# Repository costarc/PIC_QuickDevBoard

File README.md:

# PIC_QuickDevBoard
Small and simple PIC16F &amp; PIC24F Development Board with Programming Support for PICKit

Rev 2.3
- Added demo project for all three suported PIC models
- Changed LED to PORT RB4 to be compatible with the 3 PICs supported by the board
- Added missing terminals in the mini-usb custom footprint
- Changed LED resistor from 270R to 470R to avoid led light too bright
- Changed PIC16F84 /MCLR pull-up resistor from 270R to 10K

Rev 2.2
- Adjustments to mini-usb footprint
- Fixed power rails to PC16F145X that was not allowing programming the microcontroller

Rev 2.1
- Updated footprint for USB-Micro to move it to the comopnent side (vcc - gnd was inverted)
- Fix for 5V PICs (16F) with addtion o extra jumpers
- Inverted PICKIT pin header for better alignment (cosmetic change)

Rev 2.0
- Initial production version

Fabrication
-----------
Measures: 70.90 x 81.30

Usage
-----

Power Requirements - PIC16
--------------------------

For correct programing, erasing and verifying the PIC, the external porwer must be provided via the USB connector or the PIN Header.

PIC16 requires 5V - if the PIN Header is used for power, 5V should be provided in this connector.
USB connector will provide the correct 5V for the PIC16.

Power Requirements - PIC24
--------------------------

For correct programing, erasing and verifying the PIC, the external porwer must be provided via the USB connector or the PIN Header.

PIC24 requires 3.3V - if the PIN Header is used for power, 3.3V must be provided in this connector - no conversion is done for voltages provided via this connector.
USB connector will provide the correct 3.3V for the PIC24 via coversion using the LD1117 converter in the board.

Operation * Programming
-----------------------

To develop & program A PIC device, set the three jumpers in position PIC24F, PIC16F14 OR PIC16F84 depending on which device you are being used.

To program the PIC24, remove jumper "Program". Re-insert after programming.

Development Resources
---------------------
All  I/O pins are exposed thorugh the Pin Headers in the board.
Additionaly, a Pushb Button and a LED are available for quick tests and experiments.
Push Button is connected to RA0
LED is connected to RB4

These components can be removed from the board if they are not needed or if they interfere with normal operation of these signals in the Pin Headers.

Default Demonstration Firmware
------------------------------
The demonstration firmware works the same for all models - the LED on RB4 will blink slowly, but if the push button is pressed it will blink faster.

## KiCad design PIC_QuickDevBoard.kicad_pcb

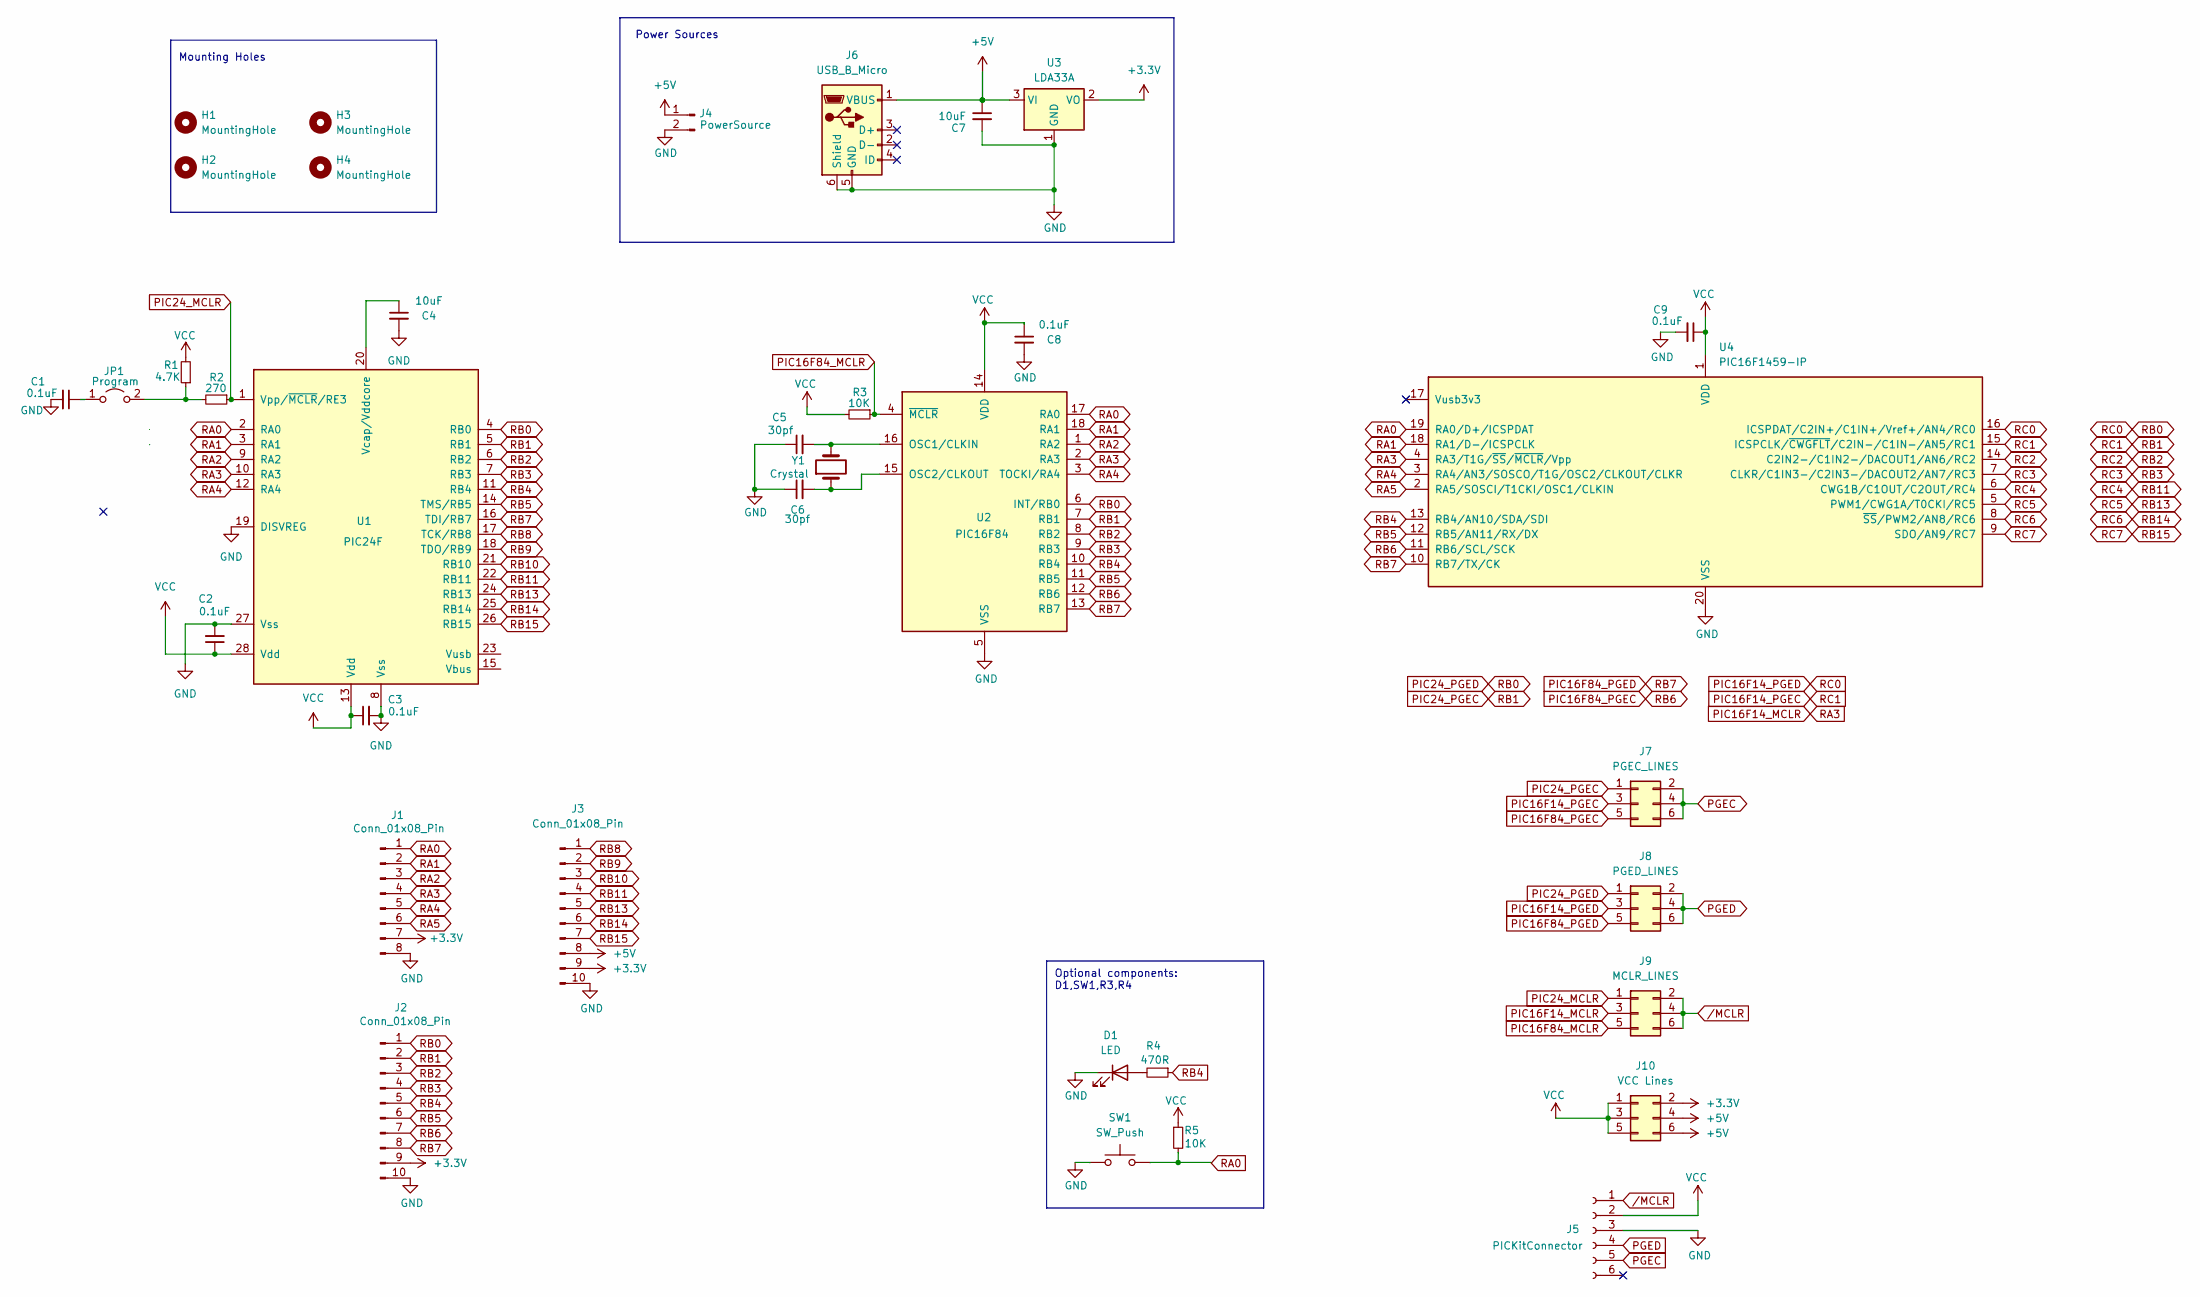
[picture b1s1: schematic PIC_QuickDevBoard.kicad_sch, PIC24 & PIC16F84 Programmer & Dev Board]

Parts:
C1, C2, C3, C8, C9: 0.1uF; C_Disc_D3.4mm_W2.1mm_P2.50mm
C4: 10uF; CP_Radial_Tantal_D4.5mm_P2.50mm
C5, C6: 30pf; C_Disc_D3.4mm_W2.1mm_P2.50mm
C7: 10uF; CP_Radial_D6.3mm_P2.50mm
D1: LED; LED_D3.0mm
H1, H2, H3, H4: MountingHole; MountingHole_2.5mm_Pad
J1: Conn_01x08_Pin; PinHeader_1x08_P2.54mm_Vertical
J2, J3: Conn_01x08_Pin; PinHeader_1x10_P2.54mm_Vertical
J4: PowerSource; PinHeader_1x02_P2.54mm_Vertical
J5: PICKitConnector; PinHeader_1x06_P2.54mm_Vertical
J6: USB_B_Micro; USB_Mini-B_Tensility_4Holes
J7: PGEC_LINES; PinHeader_2x03_P2.00mm_Vertical
J8: PGED_LINES; PinHeader_2x03_P2.00mm_Vertical
J9: MCLR_LINES; PinHeader_2x03_P2.00mm_Vertical
J10: VCC Lines; PinHeader_2x03_P2.00mm_Vertical
JP1: Program; PinHeader_1x02_P2.54mm_Vertical
R1: 4.7K; R_Axial_DIN0207_L6.3mm_D2.5mm_P7.62mm_Horizontal
R2: 270; R_Axial_DIN0207_L6.3mm_D2.5mm_P7.62mm_Horizontal
R3, R5: 10K; R_Axial_DIN0207_L6.3mm_D2.5mm_P7.62mm_Horizontal
R4: 470R; R_Axial_DIN0207_L6.3mm_D2.5mm_P7.62mm_Horizontal
SW1: SW_Push; SW_PUSH_6mm_2Holes
U1: PIC24F; DIP-28_W7.62mm
U2: PIC16F84; DIP-18_W7.62mm
U3: LDA33A; SOT-223-3_TabPin2
U4: PIC16F1459-IP; DIP-20_W7.62mm
Y1: Crystal; Crystal_HC49-U_Vertical

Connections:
+3.3V: J1.7, J2.9, J3.9, J10.2, U3.2 (VO)
+5V: C7.1, J3.8, J4.1, J6.1 (VBUS), J10.4, J10.6, U3.3 (VI)
GND: C1.2, C2.2, C3.2, C4.2, C5.1, C6.1, C7.2, C8.2, C9.2, D1.1 (K), J1.8, J2.10, J3.10, J4.2, J5.3, J6.5 (GND), J6.6 (Shield), SW1.1, U1.8 (Vss), U1.19 (DISVREG), U1.27 (Vss), U2.5 (VSS), U3.1 (GND), U4.20 (VSS)
unnamed: D1.2 (A), R4.2
unnamed: C1.1, JP1.1 (A)
unnamed: JP1.2 (B), R1.1, R2.2
unnamed: C4.1, U1.20 (Vcap/Vddcore)
unnamed: C5.2, U2.16 (OSC1/CLKIN), Y1.2
unnamed: C6.2, U2.15 (OSC2/CLKOUT), Y1.1
PGEC: J5.5, J7.2, J7.4, J7.6
PGED: J5.4, J8.2, J8.4, J8.6
PIC16F14_MCLR: J1.4, J9.3, U1.10 (RA3), U2.2 (RA3), U4.4 (RA3/T1G/~SS/~MCLR/Vpp)
PIC16F14_PGEC: J2.2, J7.1, J7.3, U1.5 (RB1), U2.7 (RB1), U4.15 (ICSPCLK/~CWGFLT/C2IN-/C1IN-/AN5/RC1)
PIC16F14_PGED: J2.1, J8.1, J8.3, U1.4 (RB0), U2.6 (INT/RB0), U4.16 (ICSPDAT/C2IN+/C1IN+/Vref+/AN4/RC0)
PIC16F84_MCLR: J9.5, R3.1, U2.4 (~MCLR)
PIC16F84_PGEC: J2.7, J7.5, U2.12 (RB6), U4.11 (RB6/SCL/SCK)
PIC16F84_PGED: J2.8, J8.5, U1.16 (TDI/RB7), U2.13 (RB7), U4.10 (RB7/TX/CK)
PIC24_MCLR: J9.1, R2.1, U1.1 (Vpp/~MCLR/RE3)
RA0: J1.1, R5.2, SW1.2, U1.2 (RA0), U2.17 (RA0), U4.19 (RA0/D+/ICSPDAT)
RA1: J1.2, U1.3 (RA1), U2.18 (RA1), U4.18 (RA1/D-/ICSPCLK)
RA2: J1.3, U1.9 (RA2), U2.1 (RA2)
RA4: J1.5, U1.12 (RA4), U2.3 (TOCKI/RA4), U4.3 (RA4/AN3/SOSCO/T1G/OSC2/CLKOUT/CLKR)
RA5: J1.6, U4.2 (RA5/SOSCI/T1CKI/OSC1/CLKIN)
RB2: J2.3, U1.6 (RB2), U2.8 (RB2), U4.14 (C2IN2-/C1IN2-/DACOUT1/AN6/RC2)
RB3: J2.4, U1.7 (RB3), U2.9 (RB3), U4.7 (CLKR/C1IN3-/C2IN3-/DACOUT2/AN7/RC3)
RB4: J2.5, R4.1, U1.11 (RB4), U2.10 (RB4), U4.13 (RB4/AN10/SDA/SDI)
RB5: J2.6, U1.14 (TMS/RB5), U2.11 (RB5), U4.12 (RB5/AN11/RX/DX)
RB8: J3.1, U1.17 (TCK/RB8)
RB9: J3.2, U1.18 (TDO/RB9)
RB10: J3.3, U1.21 (RB10)
RB11: J3.4, U1.22 (RB11), U4.6 (CWG1B/C1OUT/C2OUT/RC4)
RB13: J3.5, U1.24 (RB13), U4.5 (PWM1/CWG1A/T0CKI/RC5)
RB14: J3.6, U1.25 (RB14), U4.8 (~SS/PWM2/AN8/RC6)
RB15: J3.7, U1.26 (RB15), U4.9 (SDO/AN9/RC7)
VCC: C2.1, C3.1, C8.1, C9.1, J5.2, J10.1, J10.3, J10.5, R1.2, R3.2, R5.1, U1.13 (Vdd), U1.28 (Vdd), U2.14 (VDD), U4.1 (VDD)
/MCLR: J5.1, J9.2, J9.4, J9.6

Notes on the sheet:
Optional components: D1,SW1,R3,R4
Mounting Holes
Power Sources

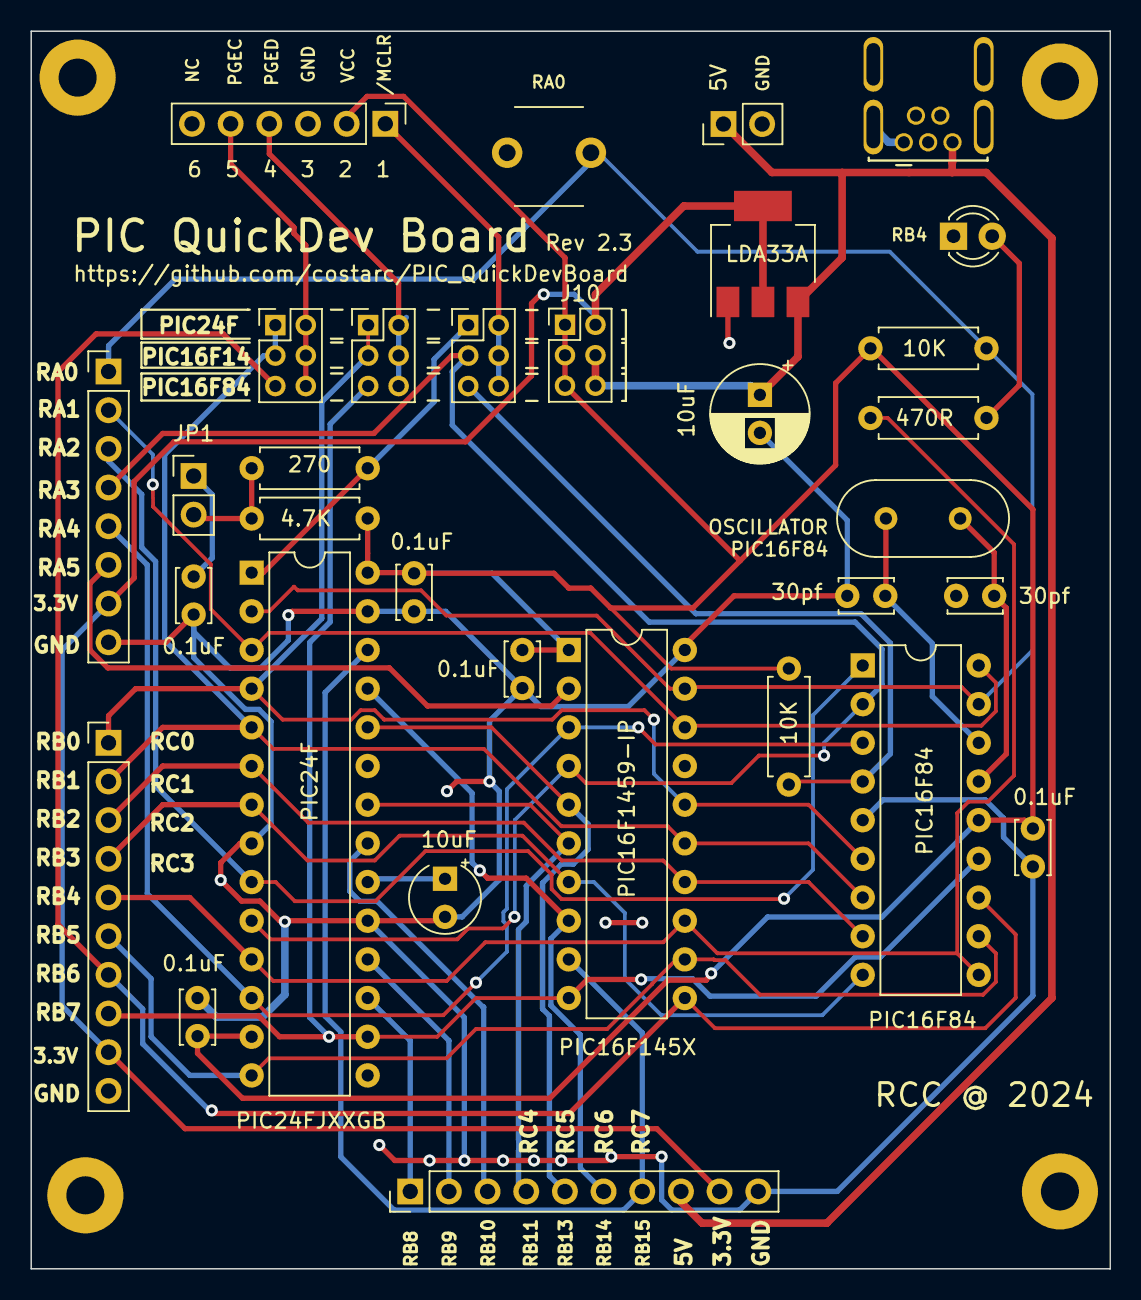
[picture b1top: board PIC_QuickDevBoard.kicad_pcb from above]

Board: 2 copper layers, 70.9 x 81.3 mm, 36 parts (0 on the bottom side), 36 nets.

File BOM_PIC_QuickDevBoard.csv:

"Reference","Value","Datasheet","Footprint","Qty","DNP"
"C1,C2,C3,C8,C9","0.1uF","~","Capacitor_THT:C_Disc_D3.4mm_W2.1mm_P2.50mm","5",""
"C4,C7","10uF","~","-- mixed values --","2",""
"C5,C6","30pf","~","Capacitor_THT:C_Disc_D3.4mm_W2.1mm_P2.50mm","2",""
"D1","LED","~","LED_THT:LED_D3.0mm","1",""
"H1,H2,H3,H4","MountingHole","~","MountingHole:MountingHole_2.5mm_Pad","4",""
"J1,J2,J3","Conn_01x08_Pin","~","-- mixed values --","3",""
"J4","PowerSource","~","Connector_PinHeader_2.54mm:PinHeader_1x02_P2.54mm_Vertical","1",""
"J5","PICKitConnector","~","Connector_PinHeader_2.54mm:PinHeader_1x06_P2.54mm_Vertical","1",""
"J6","USB_B_Micro","~","Roni_Footprints:USB_Mini-B_Tensility_4Holes","1",""
"J7","PGEC_LINES","~","Connector_PinHeader_2.00mm:PinHeader_2x03_P2.00mm_Vertical","1",""
"J8","PGED_LINES","~","Connector_PinHeader_2.00mm:PinHeader_2x03_P2.00mm_Vertical","1",""
"J9","MCLR_LINES","~","Connector_PinHeader_2.00mm:PinHeader_2x03_P2.00mm_Vertical","1",""
"J10","VCC Lines","~","Connector_PinHeader_2.00mm:PinHeader_2x03_P2.00mm_Vertical","1",""
"JP1","Program","~","Connector_PinHeader_2.54mm:PinHeader_1x02_P2.54mm_Vertical","1",""
"R1","4.7K","~","Resistor_THT:R_Axial_DIN0207_L6.3mm_D2.5mm_P7.62mm_Horizontal","1",""
"R2","270","~","Resistor_THT:R_Axial_DIN0207_L6.3mm_D2.5mm_P7.62mm_Horizontal","1",""
"R3,R5","10K","~","Resistor_THT:R_Axial_DIN0207_L6.3mm_D2.5mm_P7.62mm_Horizontal","2",""
"R4","470R","~","Resistor_THT:R_Axial_DIN0207_L6.3mm_D2.5mm_P7.62mm_Horizontal","1",""
"SW1","SW_Push","~","Roni_Footprints:SW_PUSH_6mm_2Holes","1",""
"U1","PIC24F","http://ww1.microchip.com/downloads/en/DeviceDoc/41452B.pdf","Package_DIP:DIP-28_W7.62mm","1",""
"U2","PIC16F84","http://ww1.microchip.com/downloads/en/DeviceDoc/30430c.pdf","Package_DIP:DIP-18_W7.62mm","1",""
"U3","LDA33A","http://www.st.com/st-web-ui/static/active/en/resource/techni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","Package_TO_SOT_SMD:SOT-223-3_TabPin2","1",""
"U4","PIC16F1459-IP","http://ww1.microchip.com/downloads/en/DeviceDoc/41639A.pdf","Package_DIP:DIP-20_W7.62mm","1",""
"Y1","Crystal","~","Crystal:Crystal_HC49-U_Vertical","1",""

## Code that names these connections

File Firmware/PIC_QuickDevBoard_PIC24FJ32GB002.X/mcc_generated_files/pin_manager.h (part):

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*/
/**
  @Summary
    Sets the GPIO pin, RA0, high using LATA0.

  @Description
    Sets the GPIO pin, RA0, high using LATA0.

  @Preconditions
    The RA0 must be set to an output.
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#define BUTTON_SetHigh()          (_LATA0 = 1)
/**
  @Summary
    Sets the GPIO pin, RA0, low using LATA0.

  @Description
    Sets the GPIO pin, RA0, low using LATA0.

  @Preconditions
    The RA0 must be set to an output.
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#define BUTTON_SetLow()           (_LATA0 = 0)
/**
  @Summary
    Toggles the GPIO pin, RA0, using LATA0.

  @Description
    Toggles the GPIO pin, RA0, using LATA0.

  @Preconditions
    The RA0 must be set to an output.
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#define BUTTON_Toggle()           (_LATA0 ^= 1)
/**
  @Summary
    Reads the value of the GPIO pin, RA0.

  @Description
    Reads the value of the GPIO pin, RA0.

  @Preconditions
    None.
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    </code>

*/
#define BUTTON_GetValue()         _RA0
/**
  @Summary
    Configures the GPIO pin, RA0, as an input.

  @Description
    Configures the GPIO pin, RA0, as an input.

  @Preconditions
    None.
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#define BUTTON_SetDigitalInput()  (_TRISA0 = 1)
/**
  @Summary
    Configures the GPIO pin, RA0, as an output.

  @Description
    Configures the GPIO pin, RA0, as an output.

  @Preconditions
    None.
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#define BUTTON_SetDigitalOutput() (_TRISA0 = 0)
/**
  @Summary
    Sets the GPIO pin, RA1, high using LATA1.

  @Description
    Sets the GPIO pin, RA1, high using LATA1.

  @Preconditions
    The RA1 must be set to an output.
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#define IO_RA1_SetHigh()          (_LATA1 = 1)
/**
  @Summary
    Sets the GPIO pin, RA1, low using LATA1.

  @Description
    Sets the GPIO pin, RA1, low using LATA1.

  @Preconditions
    The RA1 must be set to an output.
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#define IO_RA1_SetLow()           (_LATA1 = 0)
/**
  @Summary
    Toggles the GPIO pin, RA1, using LATA1.

  @Description
    Toggles the GPIO pin, RA1, using LATA1.

  @Preconditions
    The RA1 must be set to an output.
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#define IO_RA1_Toggle()           (_LATA1 ^= 1)
/**
  @Summary
    Reads the value of the GPIO pin, RA1.

  @Description
    Reads the value of the GPIO pin, RA1.

  @Preconditions
    None.
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    </code>

*/
#define IO_RA1_GetValue()         _RA1
/**
  @Summary
    Configures the GPIO pin, RA1, as an input.

  @Description
    Configures the GPIO pin, RA1, as an input.

  @Preconditions
    None.
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#define IO_RA1_SetDigitalInput()  (_TRISA1 = 1)
/**
  @Summary
    Configures the GPIO pin, RA1, as an output.

  @Description
    Configures the GPIO pin, RA1, as an output.

  @Preconditions
    None.
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#define IO_RA1_SetDigitalOutput() (_TRISA1 = 0)
/**
  @Summary
    Sets the GPIO pin, RA2, high using LATA2.

  @Description
    Sets the GPIO pin, RA2, high using LATA2.

  @Preconditions
    The RA2 must be set to an output.
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#define IO_RA2_SetHigh()          (_LATA2 = 1)
/**
  @Summary
    Sets the GPIO pin, RA2, low using LATA2.

  @Description
    Sets the GPIO pin, RA2, low using LATA2.

  @Preconditions
    The RA2 must be set to an output.
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#define IO_RA2_SetLow()           (_LATA2 = 0)
/**
  @Summary
    Toggles the GPIO pin, RA2, using LATA2.

  @Description
    Toggles the GPIO pin, RA2, using LATA2.

  @Preconditions
    The RA2 must be set to an output.
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#define IO_RA2_Toggle()           (_LATA2 ^= 1)
/**
  @Summary
    Reads the value of the GPIO pin, RA2.

  @Description
    Reads the value of the GPIO pin, RA2.

  @Preconditions
    None.
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    </code>

*/
#define IO_RA2_GetValue()         _RA2
/**
  @Summary
    Configures the GPIO pin, RA2, as an input.

  @Description
    Configures the GPIO pin, RA2, as an input.

  @Preconditions
    None.
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#define IO_RA2_SetDigitalInput()  (_TRISA2 = 1)
/**
  @Summary
    Configures the GPIO pin, RA2, as an output.

  @Description
    Configures the GPIO pin, RA2, as an output.

  @Preconditions
    None.
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#define IO_RA2_SetDigitalOutput() (_TRISA2 = 0)
/**
  @Summary
    Sets the GPIO pin, RA3, high using LATA3.

  @Description
    Sets the GPIO pin, RA3, high using LATA3.

  @Preconditions
    The RA3 must be set to an output.
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#define IO_RA3_SetHigh()          (_LATA3 = 1)
/**
  @Summary
    Sets the GPIO pin, RA3, low using LATA3.

  @Description
    Sets the GPIO pin, RA3, low using LATA3.

  @Preconditions
    The RA3 must be set to an output.
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#define IO_RA3_SetLow()           (_LATA3 = 0)
/**
  @Summary
    Toggles the GPIO pin, RA3, using LATA3.

  @Description
    Toggles the GPIO pin, RA3, using LATA3.

  @Preconditions
    The RA3 must be set to an output.
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#define IO_RA3_Toggle()           (_LATA3 ^= 1)
/**
  @Summary
    Reads the value of the GPIO pin, RA3.

  @Description
    Reads the value of the GPIO pin, RA3.

  @Preconditions
    None.
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    </code>

*/
#define IO_RA3_GetValue()         _RA3
/**
  @Summary
    Configures the GPIO pin, RA3, as an input.

  @Description
    Configures the GPIO pin, RA3, as an input.

  @Preconditions
    None.
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#define IO_RA3_SetDigitalInput()  (_TRISA3 = 1)
/**
  @Summary
    Configures the GPIO pin, RA3, as an output.

  @Description
    Configures the GPIO pin, RA3, as an output.

  @Preconditions
    None.
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#define IO_RA3_SetDigitalOutput() (_TRISA3 = 0)
/**
  @Summary
    Sets the GPIO pin, RA4, high using LATA4.

  @Description
    Sets the GPIO pin, RA4, high using LATA4.

  @Preconditions
    The RA4 must be set to an output.
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#define IO_RA4_SetHigh()          (_LATA4 = 1)
/**
  @Summary
    Sets the GPIO pin, RA4, low using LATA4.

  @Description
    Sets the GPIO pin, RA4, low using LATA4.

  @Preconditions
    The RA4 must be set to an output.
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#define IO_RA4_SetLow()           (_LATA4 = 0)
/**
  @Summary
    Toggles the GPIO pin, RA4, using LATA4.

  @Description
    Toggles the GPIO pin, RA4, using LATA4.

  @Preconditions
    The RA4 must be set to an output.
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#define IO_RA4_Toggle()           (_LATA4 ^= 1)
/**
  @Summary
    Reads the value of the GPIO pin, RA4.

  @Description
    Reads the value of the GPIO pin, RA4.

  @Preconditions
    None.
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    </code>

*/
#define IO_RA4_GetValue()         _RA4
/**
  @Summary
    Configures the GPIO pin, RA4, as an input.

  @Description
    Configures the GPIO pin, RA4, as an input.

  @Preconditions
    None.
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#define IO_RA4_SetDigitalInput()  (_TRISA4 = 1)
/**
  @Summary
    Configures the GPIO pin, RA4, as an output.

  @Description
    Configures the GPIO pin, RA4, as an output.

  @Preconditions
    None.
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#define IO_RA4_SetDigitalOutput() (_TRISA4 = 0)
/**
  @Summary
    Sets the GPIO pin, RB0, high using LATB0.

  @Description
    Sets the GPIO pin, RB0, high using LATB0.

  @Preconditions
    The RB0 must be set to an output.
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#define IO_RB0_SetHigh()          (_LATB0 = 1)
/**
  @Summary
    Sets the GPIO pin, RB0, low using LATB0.

  @Description
    Sets the GPIO pin, RB0, low using LATB0.

  @Preconditions
    The RB0 must be set to an output.
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#define IO_RB0_SetLow()           (_LATB0 = 0)
/**
  @Summary
    Toggles the GPIO pin, RB0, using LATB0.

  @Description
    Toggles the GPIO pin, RB0, using LATB0.

  @Preconditions
    The RB0 must be set to an output.
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#define IO_RB0_Toggle()           (_LATB0 ^= 1)
/**
  @Summary
    Reads the value of the GPIO pin, RB0.

  @Description
    Reads the value of the GPIO pin, RB0.

  @Preconditions
    None.
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    </code>

*/
#define IO_RB0_GetValue()         _RB0
/**
  @Summary
    Configures the GPIO pin, RB0, as an input.

  @Description
    Configures the GPIO pin, RB0, as an input.

  @Preconditions
    None.
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#define IO_RB0_SetDigitalInput()  (_TRISB0 = 1)
/**
  @Summary
    Configures the GPIO pin, RB0, as an output.

  @Description
    Configures the GPIO pin, RB0, as an output.

  @Preconditions
    None.
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#define IO_RB0_SetDigitalOutput() (_TRISB0 = 0)
/**
  @Summary
    Sets the GPIO pin, RB1, high using LATB1.

  @Description
    Sets the GPIO pin, RB1, high using LATB1.

  @Preconditions
    The RB1 must be set to an output.
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#define IO_RB1_SetHigh()          (_LATB1 = 1)
/**
  @Summary
    Sets the GPIO pin, RB1, low using LATB1.

  @Description
    Sets the GPIO pin, RB1, low using LATB1.

  @Preconditions
    The RB1 must be set to an output.
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#define IO_RB1_SetLow()           (_LATB1 = 0)
/**
  @Summary
    Toggles the GPIO pin, RB1, using LATB1.

  @Description
    Toggles the GPIO pin, RB1, using LATB1.

  @Preconditions
    The RB1 must be set to an output.
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#define IO_RB1_Toggle()           (_LATB1 ^= 1)
/**
  @Summary
    Reads the value of the GPIO pin, RB1.

  @Description
    Reads the value of the GPIO pin, RB1.

  @Preconditions
    None.
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    </code>

*/
#define IO_RB1_GetValue()         _RB1
/**
  @Summary
    Configures the GPIO pin, RB1, as an input.

  @Description
    Configures the GPIO pin, RB1, as an input.

  @Preconditions
    None.
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#define IO_RB1_SetDigitalInput()  (_TRISB1 = 1)
/**
  @Summary
    Configures the GPIO pin, RB1, as an output.

  @Description
    Configures the GPIO pin, RB1, as an output.

  @Preconditions
    None.
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#define IO_RB1_SetDigitalOutput() (_TRISB1 = 0)
/**
  @Summary
    Sets the GPIO pin, RB10, high using LATB10.

  @Description
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
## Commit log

2024-04-13 fixing PICF14 vcc
2024-04-13 Updated PCB to REv 2.1 with fix to VCC for PIC16F
2024-04-19 Rev. 2.1 - Fabricated
2024-05-01 Revision 2.2
2024-05-12 Progressing with calibration code
2024-05-17 Demo firmware for PIC16F84A finished
2024-05-17 Rev2.3 - fixed mini-usb footprint and pcb routing power from it.
2024-05-19 Demo for PIC16F145X functional
2024-05-19 Rev2.3 - led on RB4 and Demo for all three suported PICs
2024-05-19 Create LICENSE
2024-05-19 IBOM.HTML Bill of Materials interactive
2024-07-14 Added Quick Start Guide

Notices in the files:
Firmware/PIC_QuickDevBoard_PIC24FJ32GB002.X/mcc_generated_files/pin_manager.h:
(c) 2020 Microchip Technology Inc. and its subsidiaries. You may use this
